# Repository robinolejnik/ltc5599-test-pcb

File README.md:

# ltc5599-test-pcb
This is a test PCB for the LTC5599 30 MHz to 1300 MHz Low Power Direct Quadrature Modulator.

[Schematic](https://raw.githubusercontent.com/robinolejnik/ltc5599-test-pcb/master/ltc5599-test-pcb.pdf)

[Interactive BOM](https://htmlpreview.github.io/?https://github.com/robinolejnik/ltc5599-test-pcb/blob/master/bom/ibom.html)

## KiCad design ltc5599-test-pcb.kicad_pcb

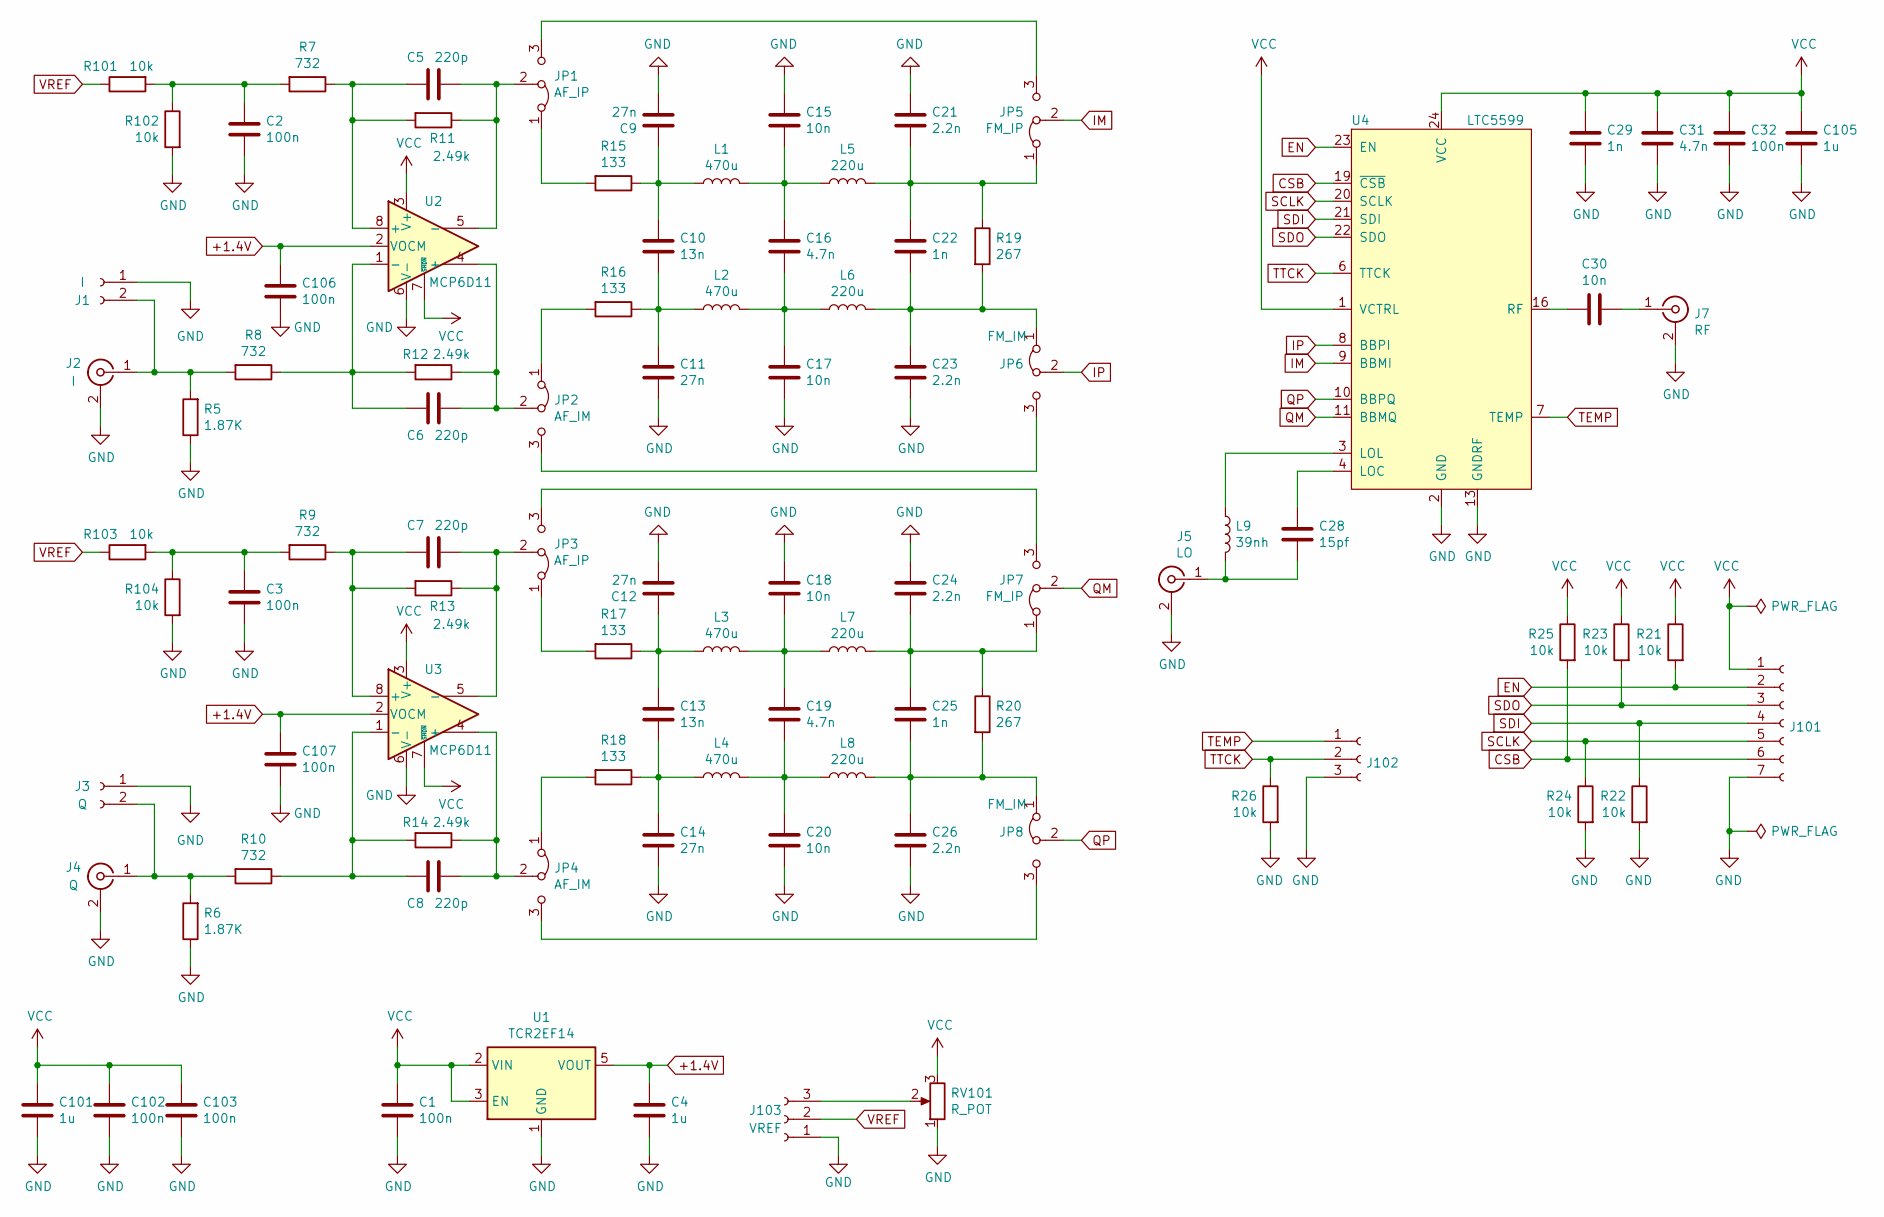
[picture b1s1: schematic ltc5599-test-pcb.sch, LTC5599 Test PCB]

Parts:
C1, C2, C3, C32, C102, C103, C106, C107: 100n; C_0805_2012Metric
C4, C101, C105: 1u; C_0805_2012Metric
C5, C6, C7, C8: 220p; C_0603_1608Metric; Mouser 603-CC603GRNPO9BN221
C9, C11, C12, C14: 27n; C_0603_1608Metric; Mouser 603-CC603JRX7R9BB273
C10, C13: 13n; C_0805_2012Metric; Mouser 81-GRM2195C1H133JA1D
C15, C17, C18, C20, C30: 10n; C_0603_1608Metric; Mouser 80-C0603C103J5R
C16, C19, C31: 4.7n; C_0603_1608Metric; Mouser 80-C0603C472F8HACTU
C21, C23, C24, C26: 2.2n; C_0603_1608Metric; Mouser 81-GCM1885C1H222FA6D
C22, C25, C29: 1n; C_0603_1608Metric; Mouser 603-CC603GRNPO9BN102
C28: 15pf; C_0603_1608Metric; Mouser 609-251R14S150JV4T
J1: I; PinHeader_1x02_P2.54mm_Vertical
J2: I; SMA_Amphenol_132289_EdgeMount
J3: Q; PinHeader_1x02_P2.54mm_Vertical
J4: Q; SMA_Amphenol_132289_EdgeMount
J5: LO; SMA_Amphenol_132289_EdgeMount
J7: RF; SMA_Amphenol_132289_EdgeMount
J101: Conn_01x07_Female; PinHeader_1x07_P2.54mm_Vertical
J102: Conn_01x03_Female; PinHeader_1x03_P2.54mm_Vertical
J103: VREF; PinHeader_1x03_P2.54mm_Vertical
JP1, JP3: AF_IP; PinHeader_1x03_P2.54mm_Vertical
JP2, JP4: AF_IM; PinHeader_1x03_P2.54mm_Vertical
JP5, JP7: FM_IP; PinHeader_1x03_P2.54mm_Vertical
JP6, JP8: FM_IM; PinHeader_1x03_P2.54mm_Vertical
L1, L2, L3, L4: 470u; L_Bourns-SRR7045; Mouser 652-SRR7045-471M
L5, L6, L7, L8: 220u; L_Bourns-SRR7045; Mouser 652-SRR7045-221M
L9: 39nh; L_0603_1608Metric; Mouser 81-LQW18AS39NG00D
R5, R6: 1.87K; R_0603_1608Metric
R7, R8, R9, R10: 732; R_0603_1608Metric; Mouser 652-CR0603FX-7320ELF
R11, R12, R13, R14: 2.49k; R_0603_1608Metric; Mouser 652-CR0603FX-2491ELF
R15, R16, R17, R18: 133; R_0603_1608Metric; Mouser 603-RC0603FR-07133RL
R19, R20: 267; R_0603_1608Metric; Mouser 603-RC0603FR-07267RL
R21, R22, R23, R24, R25, R26, R101, R102, R103, R104: 10k; R_0805_2012Metric
RV101: R_POT; Potentiometer_ACP_CA9-H2,5_Horizontal
U1: TCR2EF14; TSOT-23-5; Mouser 757-TCR2EF14LMCT
U2, U3: MCP6D11; MSOP-8_3x3mm_P0.65mm; Mouser 579-MCP6D11T-E/MS
U4: LTC5599; QFN-24-1EP_4x4mm_P0.5mm_EP2.6x2.6mm

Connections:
+1.4V: C4.1, C106.1, C107.1, U1.5 (VOUT), U2.2 (VOCM), U3.2 (VOCM)
CSB: J101.6, R25.2, U4.19 (~CSB)
EN: J101.2, R21.2, U4.23 (EN)
GND: C1.2, C2.2, C3.2, C4.2, C9.2, C11.2, C12.2, C14.2, C15.1, C17.2, C18.1, C20.2, C21.1, C23.2, C24.1, C26.2, C29.2, C31.2, C32.2, C101.2, C102.2, C103.2, C105.2, C106.2, C107.2, J1.1, J2.2 (Ext), J3.1, J4.2 (Ext), J5.2 (Ext), J7.2 (Ext), J101.7, J102.3, J103.1, R5.1, R6.1, R22.2, R24.2, R26.2, R102.2, R104.2, RV101.1, U1.1 (GND), U2.6 (V-), U3.6 (V-), U4.2 (GND), U4.5 (GND), U4.12 (GND), U4.13 (GNDRF), U4.14 (GNDRF), U4.15 (GNDRF), U4.17 (GNDRF), U4.18 (GNDRF), U4.25 (GND)
IM: JP5.2 (C), U4.9 (BBMI)
IP: JP6.2 (C), U4.8 (BBPI)
unnamed: C2.1, R7.2, R101.2, R102.1
unnamed: C3.1, R9.2, R103.2, R104.1
unnamed: C5.1, JP1.2 (C), R11.1, U2.5 (-)
unnamed: C5.2, R7.1, R11.2, U2.8 (+)
unnamed: C6.1, JP2.2 (C), R12.1, U2.4 (+)
unnamed: C6.2, R8.1, R12.2, U2.1 (-)
unnamed: C7.1, JP3.2 (C), R13.1, U3.5 (-)
unnamed: C7.2, R9.1, R13.2, U3.8 (+)
unnamed: C8.1, JP4.2 (C), R14.1, U3.4 (+)
unnamed: C8.2, R10.1, R14.2, U3.1 (-)
unnamed: C9.1, C10.1, L1.1, R15.1
unnamed: C10.2, C11.1, L2.1, R16.1
unnamed: C12.1, C13.1, L3.1, R17.1
unnamed: C13.2, C14.1, L4.1, R18.1
unnamed: C15.2, C16.1, L1.2, L5.1
unnamed: C16.2, C17.1, L2.2, L6.1
unnamed: C18.2, C19.1, L3.2, L7.1
unnamed: C19.2, C20.1, L4.2, L8.1
unnamed: C21.2, C22.1, JP5.1 (A), L5.2, R19.1
unnamed: C22.2, C23.1, JP6.1 (A), L6.2, R19.2
unnamed: C24.2, C25.1, JP7.1 (A), L7.2, R20.1
unnamed: C25.2, C26.1, JP8.1 (A), L8.2, R20.2
unnamed: C28.1, U4.4 (LOC)
unnamed: C28.2, J5.1 (In), L9.2
unnamed: C30.1, J7.1 (In)
unnamed: C30.2, U4.16 (RF)
unnamed: J1.2, J2.1 (In), R5.2, R8.2
unnamed: J3.2, J4.1 (In), R6.2, R10.2
unnamed: J103.3, RV101.2
unnamed: JP1.1 (A), R15.2
unnamed: JP1.3 (B), JP5.3 (B)
unnamed: JP2.1 (A), R16.2
unnamed: JP2.3 (B), JP6.3 (B)
unnamed: JP3.1 (A), R17.2
unnamed: JP3.3 (B), JP7.3 (B)
unnamed: JP4.1 (A), R18.2
unnamed: JP4.3 (B), JP8.3 (B)
unnamed: L9.1, U4.3 (LOL)
QM: JP7.2 (C), U4.11 (BBMQ)
QP: JP8.2 (C), U4.10 (BBPQ)
SCLK: J101.5, R24.1, U4.20 (SCLK)
SDI: J101.4, R22.1, U4.21 (SDI)
SDO: J101.3, R23.2, U4.22 (SDO)
TEMP: J102.1, U4.7 (TEMP)
TTCK: J102.2, R26.1, U4.6 (TTCK)
VCC: C1.1, C29.1, C31.1, C32.1, C101.1, C102.1, C103.1, C105.1, J101.1, R21.1, R23.1, R25.1, RV101.3, U1.2 (VIN), U1.3 (EN), U2.3 (V+), U2.7 (~SHDN), U3.3 (V+), U3.7 (~SHDN), U4.1 (VCTRL), U4.24 (VCC)
VREF: J103.2, R101.1, R103.1

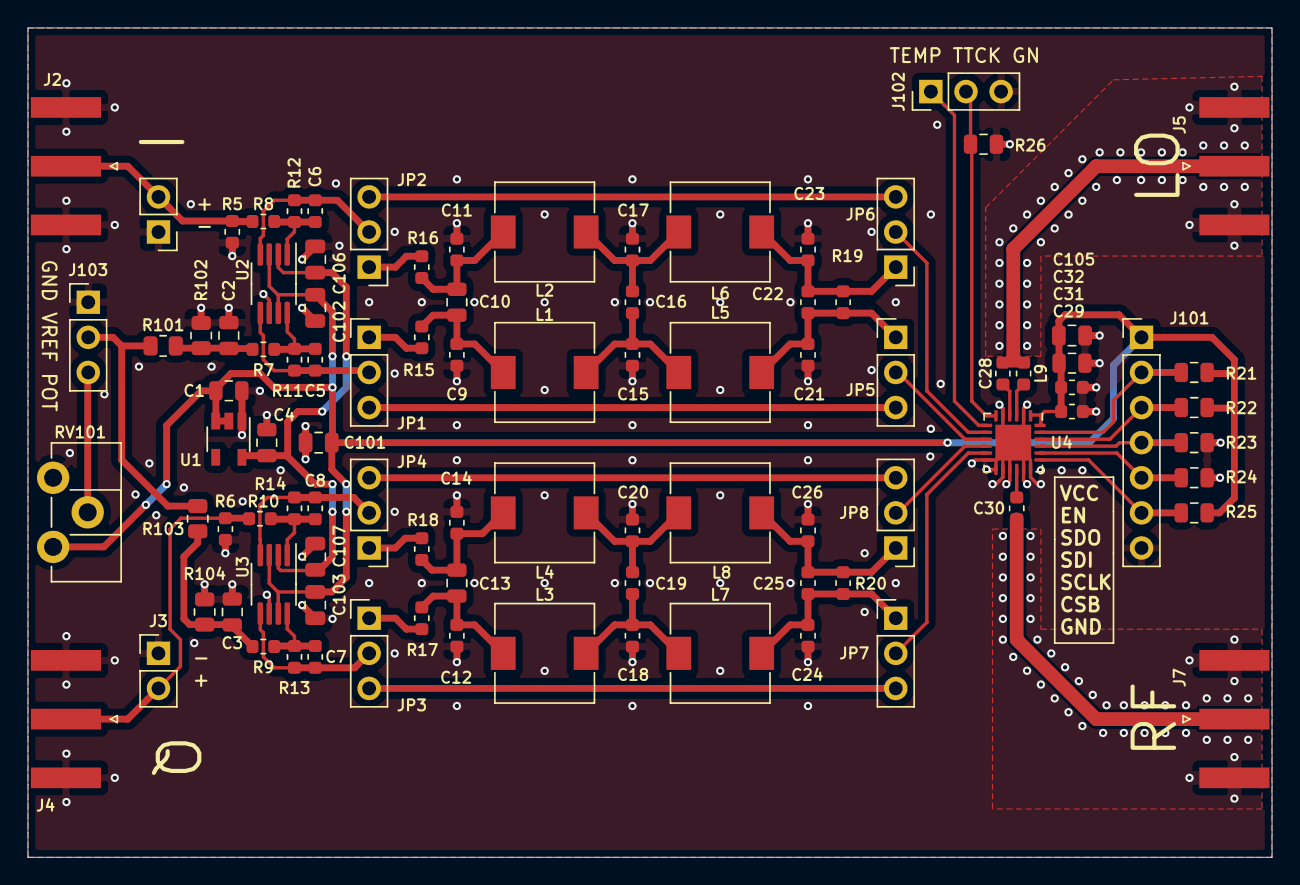
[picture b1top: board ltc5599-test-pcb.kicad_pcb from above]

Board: 2 copper layers, 90.0 x 60.0 mm, 94 parts (0 on the bottom side), 53 nets.

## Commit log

2020-12-12 added project files

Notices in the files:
ltc5599-test-pcb.kicad_pcb:
License: MIT
